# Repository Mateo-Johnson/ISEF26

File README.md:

# **EDGE-A/B Overall Design (ESP32-S3-WROOM-1-N16R8)**

**EDGE-A (Expanded Model, General):**

* Dual CPU/MCU System  
  * EDGE-A uses a single ESP32-S3 and a single RP2350 dual-core ARM Cortex-M0+, with the S3 handling high-level coordination, wireless communication (WiFi/Bluetooth), audio processing, data logging, user interface, and system management, while the RP2350 serves as the dedicated real-time processing unit for precise motor control, quadrature encoder processing, sensor fusion (gyroscope \+ TOF), PWM generation, and all timing-critical operations.  
  * The two will communicate over dedicated high speed UART  
* **ESP32-S3 based (ESP32-S3-WROOM-1)**  
  * N16R8  
  * 2.4 GHz Wifi (802.11 b/g/n)  
  * Bluetooth 5.0 (LE)  
  * USB-C (USB4085-GF-A)  
  * Interrupt-capable GPIO pins for encoders/switches  
    * Analog comparators for limit switches  
    * Hardware quadrature encoder inputs (4 channels)  
  * Low-power sleep modes  
    * Light Sleep Mode  
      * CPU is paused, RTC and ULP co-processor are running.  
      * Peripherals (like WiFi, BT) can stay connected.  
      * Wakeup sources: Timer, GPIO, ULP, etc.  
      * Lower power consumption than active mode.  
    * Deep Sleep Mode  
      * CPU, most RAM, and peripherals are powered down.  
      * Only RTC memory and ULP remain active.  
      * Very low power (tens of µA).  
      * Wakeup sources: RTC Timer, GPIO, ULP.  
* **RP2354B**  
  * External 128MB flash memory (W25Q128JVS)  
  * External Crystal (ABM8-272-T3)  
* **I/O OUT \- Check GPIO Diagram**  
  * 10 PIO pins (5 pairs) \- maximizes the RP2354B strength  
  * 2 ADC pins \- essential for motor feedback  
  * I/O can be male/female dupont  
* Distance TOF Sensor (VL53L0CXV0DH1)  
* Gyroscope (ICM-20948)  
  * Motion Interrupted Logging (MIL): only log while moving  
* USB-C/Battery Power  
  * Battery monitoring/protection circuit  
* On-board voltage regulation (3.3V, 5V, GND rails)  
* 3 PWM control channels  
  * 2 integrated DC motor drivers (DRV8833)  
* 3 Servo Connections (GND, 5V, I/O)  
* MicroSD Card Slot (TF-115)  
* 3x RGB LED (WS2812B)  
* Onboard Microphone (ICS-43434)  
* Internal USB hub IC (CH334R)  
  * Single USB-C connector routes to the hub  
  * Hub connects to both ESP32-S3 and RP2354B USB lines  
  * Each processor appears as separate COM ports on computer  
* ~~LoRa/LoRaWAN Communication (Wio-SX1262)~~  
* Battery Charger Circuit (MP2607DL-LF-Z)

**EDGE-B (Expanded Model, Machine Learning):**

* Dual CPU/MCU System  
  * EDGE-B uses a single **ESP32-S3** and a single **Kendryte K210 (Sipeed M1)**, the S3 for high-level planning, sensor fusion (gyro \+ TOF), wireless communication, audio processing, data logging, user interface, and the K210 for AI and ML applications.  
  * The two will communicate over dedicated high speed UART and distribute tasks/share larger pieces of information via shared EEPROM.  
  * Ideally, a MAIX M1 chip would be used instead of a bare K210, but if needed, a bare K210 will do.  
* **ESP32-S3 (ESP32-S3-WROOM-1)**  
  * N16R8  
  * 2.4 GHz Wifi (802.11 b/g/n)  
  * Bluetooth 5.0 (LE)  
  * USB-C (USB4085-GF-A)  
  * Interrupt-capable GPIO pins for encoders/switches  
    * Analog comparators for limit switches  
    * Hardware quadrature encoder inputs (PCNT)  
  * Low-power sleep modes  
    * Light Sleep Mode  
      * CPU is paused, RTC and ULP co-processor are running.  
      * Peripherals (like WiFi, BT) can stay connected.  
      * Wakeup sources: Timer, GPIO, ULP, etc.  
      * Lower power consumption than active mode.  
    * Deep Sleep Mode  
      * CPU, most RAM, and peripherals are powered down.  
      * Only RTC memory and ULP remain active.  
      * Very low power (tens of µA).  
      * Wakeup sources: RTC Timer, GPIO, ULP.  
* **K210 based (Sipeed MAiX module or bare chip)**  
* I/O OUT \- Check GPIO Diagram  
* Camera Input for OV2640 (FPC footprint cable)  
  * Connected to the K210  
* Gyroscope (ICM-20948)  
  * Motion Interrupted Logging (MIL): only log while moving  
* USB-C/Battery Power  
  * Battery monitoring/protection circuit  
* On-board voltage regulation (3.3V, 5V, GND rails)  
* 2 PWM control channels  
  * 2 integrated DC motor drivers (DRV8833)  
* MicroSD Card Slot (TF-115)  
* 3x RGB LED (WS2812B)  
* Onboard Microphone (ICS-43434)  
* EEPROM shared 128MB storage (CAT24M01W)  
* Ribbon Cable Input (OV2640)  
* Internal USB hub IC (CH334R)  
  * Single USB-C connector routes to the hub  
  * Hub connects to both ESP32-S3 and K210 USB lines  
  * Each processor appears as separate COM ports on computer  
* **K210** \- USB-to-UART bridge (CH340N)  
* **K210** will also need a dedicated 16MB of flash storage  
* Battery Charger Circuit (MP2607DL-LF-Z)

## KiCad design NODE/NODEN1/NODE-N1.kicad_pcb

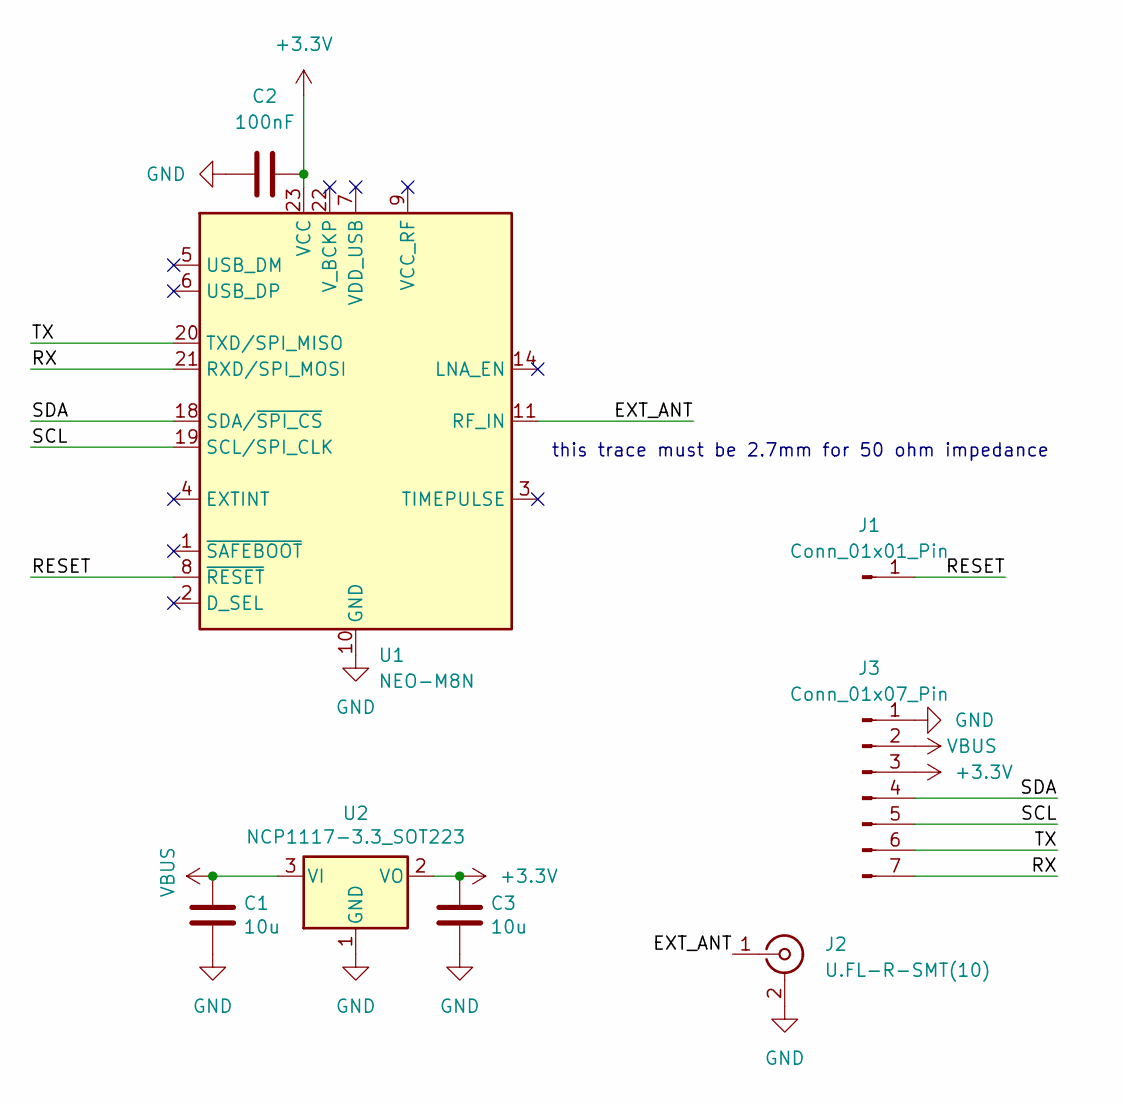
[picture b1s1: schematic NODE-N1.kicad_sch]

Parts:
C1, C3: 10u; C_0805_2012Metric
C2: 100nF; C0402
J1: Conn_01x01_Pin; TestPoint_Pad_1.5x1.5mm
J2: U.FL-R-SMT(10); U.FL_Hirose_U.FL-R-SMT-1_Vertical
J3: Conn_01x07_Pin; PinHeader_1x07_P2.54mm_Vertical
U1: NEO-M8N; ublox_NEO
U2: NCP1117-3.3_SOT223; SOT-223-3_TabPin2

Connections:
+3.3V: C2.2, C3.1, J3.3, U1.23 (VCC), U2.2 (VO)
/EXT_ANT: J2.1 (In), U1.11 (RF_IN)
/RESET: J1.1, U1.8 (~RESET)
/RX: J3.7, U1.21 (RXD/SPI_MOSI)
/SCL: J3.5, U1.19 (SCL/SPI_CLK)
/SDA: J3.4, U1.18 (SDA/~SPI_CS)
/TX: J3.6, U1.20 (TXD/SPI_MISO)
GND: C1.2, C2.1, C3.2, J2.2 (Ext), J3.1, U1.10 (GND), U1.12 (GND), U1.13 (GND), U1.24 (GND), U2.1 (GND)
VBUS: C1.1, J3.2, U2.3 (VI)

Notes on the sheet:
this trace must be 2.7mm for 50 ohm impedance

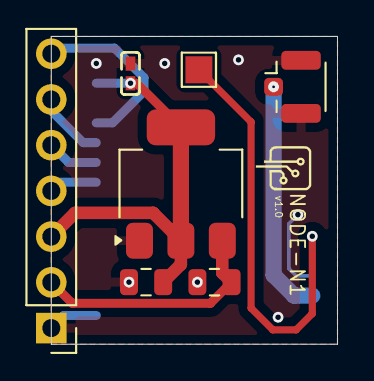
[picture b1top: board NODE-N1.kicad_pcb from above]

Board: 2 copper layers, 15.9 x 17.1 mm, 8 parts (1 on the bottom side), 9 nets.

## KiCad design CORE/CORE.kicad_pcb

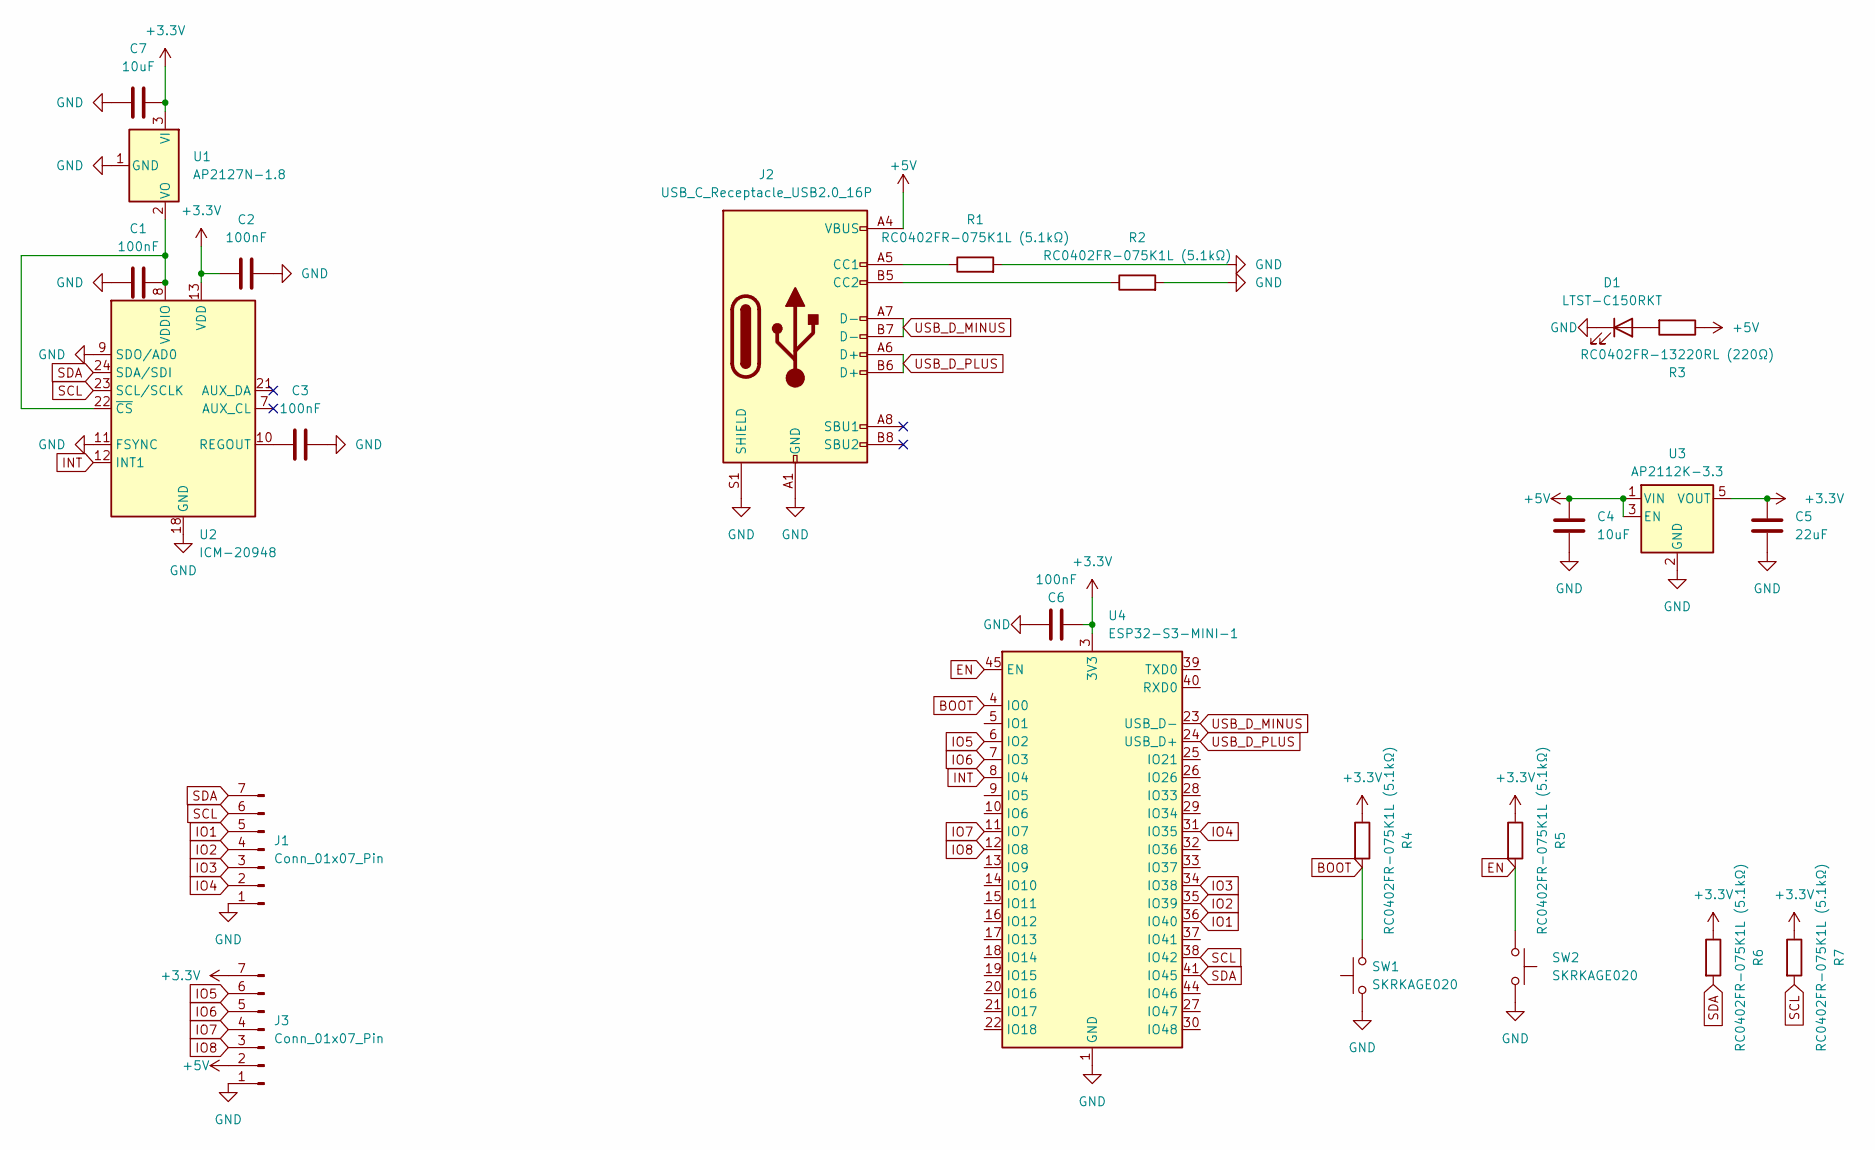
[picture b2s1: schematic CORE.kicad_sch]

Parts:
C1, C2, C3, C6: 100nF; C0402
C4, C7: 10uF; C0402
C5: 22uF; C0402
D1: LTST-C150RKT; LED_1206_3216Metric
J1, J3: Conn_01x07_Pin; PinHeader_1x07_P2.54mm_Vertical
J2: USB_C_Receptacle_USB2.0_16P; USB_C_Receptacle_HCTL_HC-TYPE-C-16P-01A
R1, R2, R4, R5, R6, R7: RC0402FR-075K1L (5.1kΩ); R0402
R3: RC0402FR-13220RL (220Ω); R0402
SW1, SW2: SKRKAGE020; SW_Push_SPST_NO_Alps_SKRK
U1: AP2127N-1.8; SOT-23
U2: ICM-20948; InvenSense_QFN-24_3x3mm_P0.4mm
U3: AP2112K-3.3; SOT-23-5
U4: ESP32-S3-MINI-1; ESP32-S2-MINI-1

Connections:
+3.3V: C2.1, C5.1, C6.2, C7.2, J3.7, R4.1, R5.1, R6.1, R7.1, U1.3 (VI), U2.13 (VDD), U3.5 (VOUT), U4.3 (3V3)
+5V: C4.1, J2.A4 (VBUS), J2.A9 (VBUS), J2.B4 (VBUS), J2.B9 (VBUS), J3.2, R3.1, U3.1 (VIN), U3.3 (EN)
BOOT: R4.2, SW1.2, U4.4 (IO0)
EN: R5.2, SW2.1, U4.45 (EN)
GND: C1.1, C2.2, C3.2, C4.2, C5.2, C6.1, C7.1, D1.1 (K), J1.1, J2.A1 (GND), J2.A12 (GND), J2.B1 (GND), J2.B12 (GND), J2.S1 (SHIELD), J3.1, R1.2, R2.2, SW1.1, SW2.2, U1.1 (GND), U2.9 (SDO/AD0), U2.11 (FSYNC), U2.18 (GND), U2.20 (GND), U3.2 (GND), U4.1 (GND), U4.2 (GND), U4.42 (GND), U4.43 (GND), U4.46 (GND), U4.47 (GND), U4.48 (GND), U4.49 (GND), U4.50 (GND), U4.51 (GND), U4.52 (GND), U4.53 (GND), U4.54 (GND), U4.55 (GND), U4.56 (GND), U4.57 (GND), U4.58 (GND), U4.59 (GND), U4.60 (GND), U4.61 (GND), U4.62 (GND), U4.63 (GND), U4.64 (GND), U4.65 (GND)
INT: U2.12 (INT1), U4.8 (IO4)
IO1: J1.5, U4.36 (IO40)
IO2: J1.4, U4.35 (IO39)
IO3: J1.3, U4.34 (IO38)
IO4: J1.2, U4.31 (IO35)
IO5: J3.6, U4.6 (IO2)
IO6: J3.5, U4.7 (IO3)
IO7: J3.4, U4.11 (IO7)
IO8: J3.3, U4.12 (IO8)
unnamed: D1.2 (A), R3.2
unnamed: J2.A5 (CC1), R1.1
unnamed: J2.B5 (CC2), R2.1
unnamed: C1.2, U1.2 (VO), U2.8 (VDDIO), U2.22 (~CS)
unnamed: C3.1, U2.10 (REGOUT)
SCL: J1.6, R7.2, U2.23 (SCL/SCLK), U4.38 (IO42)
SDA: J1.7, R6.2, U2.24 (SDA/SDI), U4.41 (IO45)
USB_D_MINUS: J2.A7 (D-), J2.B7 (D-), U4.23 (USB_D-)
USB_D_PLUS: J2.A6 (D+), J2.B6 (D+), U4.24 (USB_D+)

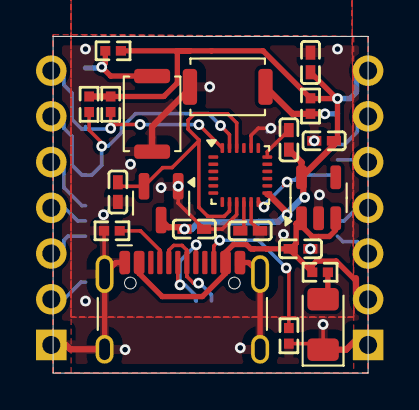
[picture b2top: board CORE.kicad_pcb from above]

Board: 2 copper layers, 17.5 x 18.7 mm, 24 parts (1 on the bottom side), 23 nets.

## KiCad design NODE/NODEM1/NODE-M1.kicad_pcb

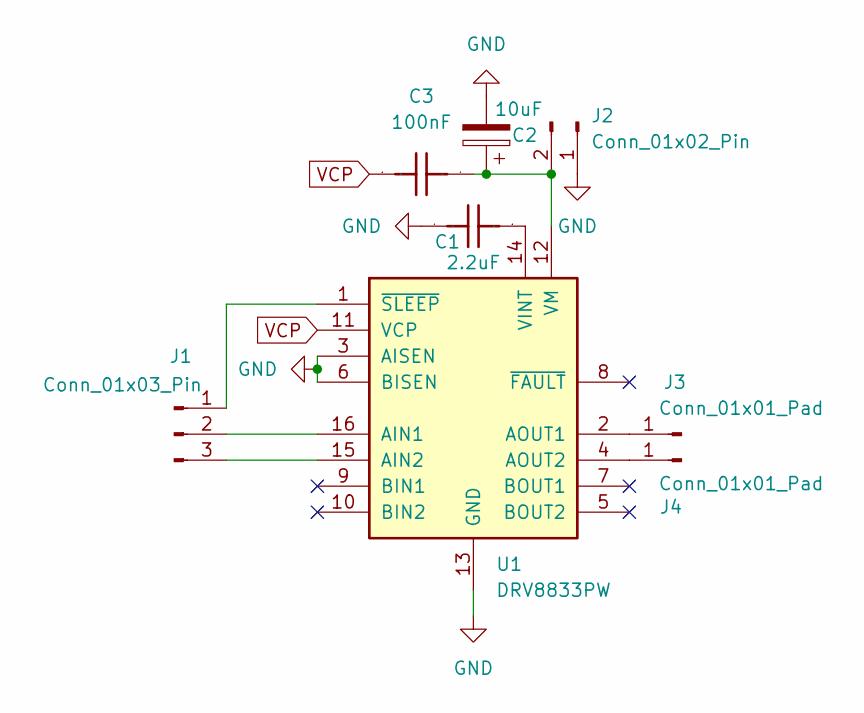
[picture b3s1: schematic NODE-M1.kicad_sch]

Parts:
C1: 2.2uF; GRM155R60J225KE01D; Manufacturer Part GRM155R60J225KE01D
C2: 10uF; TAJA106K016RNJ
C3: 100nF; CC0805KRX7R9BB104; Manufacturer Part CC0805KRX7R9BB104
J1: Conn_01x03_Pin; PinHeader_1x03_P2.54mm_Vertical
J2: Conn_01x02_Pin; PinHeader_1x02_P2.54mm_Vertical
J3, J4: Conn_01x01_Pad; TestPoint_Pad_1.5x1.5mm
U1: DRV8833PW; TSSOP-16_4.4x5mm_P0.65mm

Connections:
GND: C1.2, C2.2, J2.1, U1.3 (AISEN), U1.6 (BISEN), U1.13 (GND)
unnamed: J1.1, U1.1 (~SLEEP)
unnamed: J1.2, U1.16 (AIN1)
unnamed: J1.3, U1.15 (AIN2)
unnamed: C2.1, C3.2, J2.2, U1.12 (VM)
unnamed: J3.1, U1.2 (AOUT1)
unnamed: J4.1, U1.4 (AOUT2)
unnamed: C1.1, U1.14 (VINT)
VCP: C3.1, U1.11 (VCP)

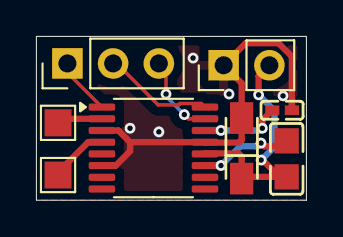
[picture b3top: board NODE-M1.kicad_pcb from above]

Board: 2 copper layers, 15.0 x 9.1 mm, 8 parts (0 on the bottom side), 9 nets.

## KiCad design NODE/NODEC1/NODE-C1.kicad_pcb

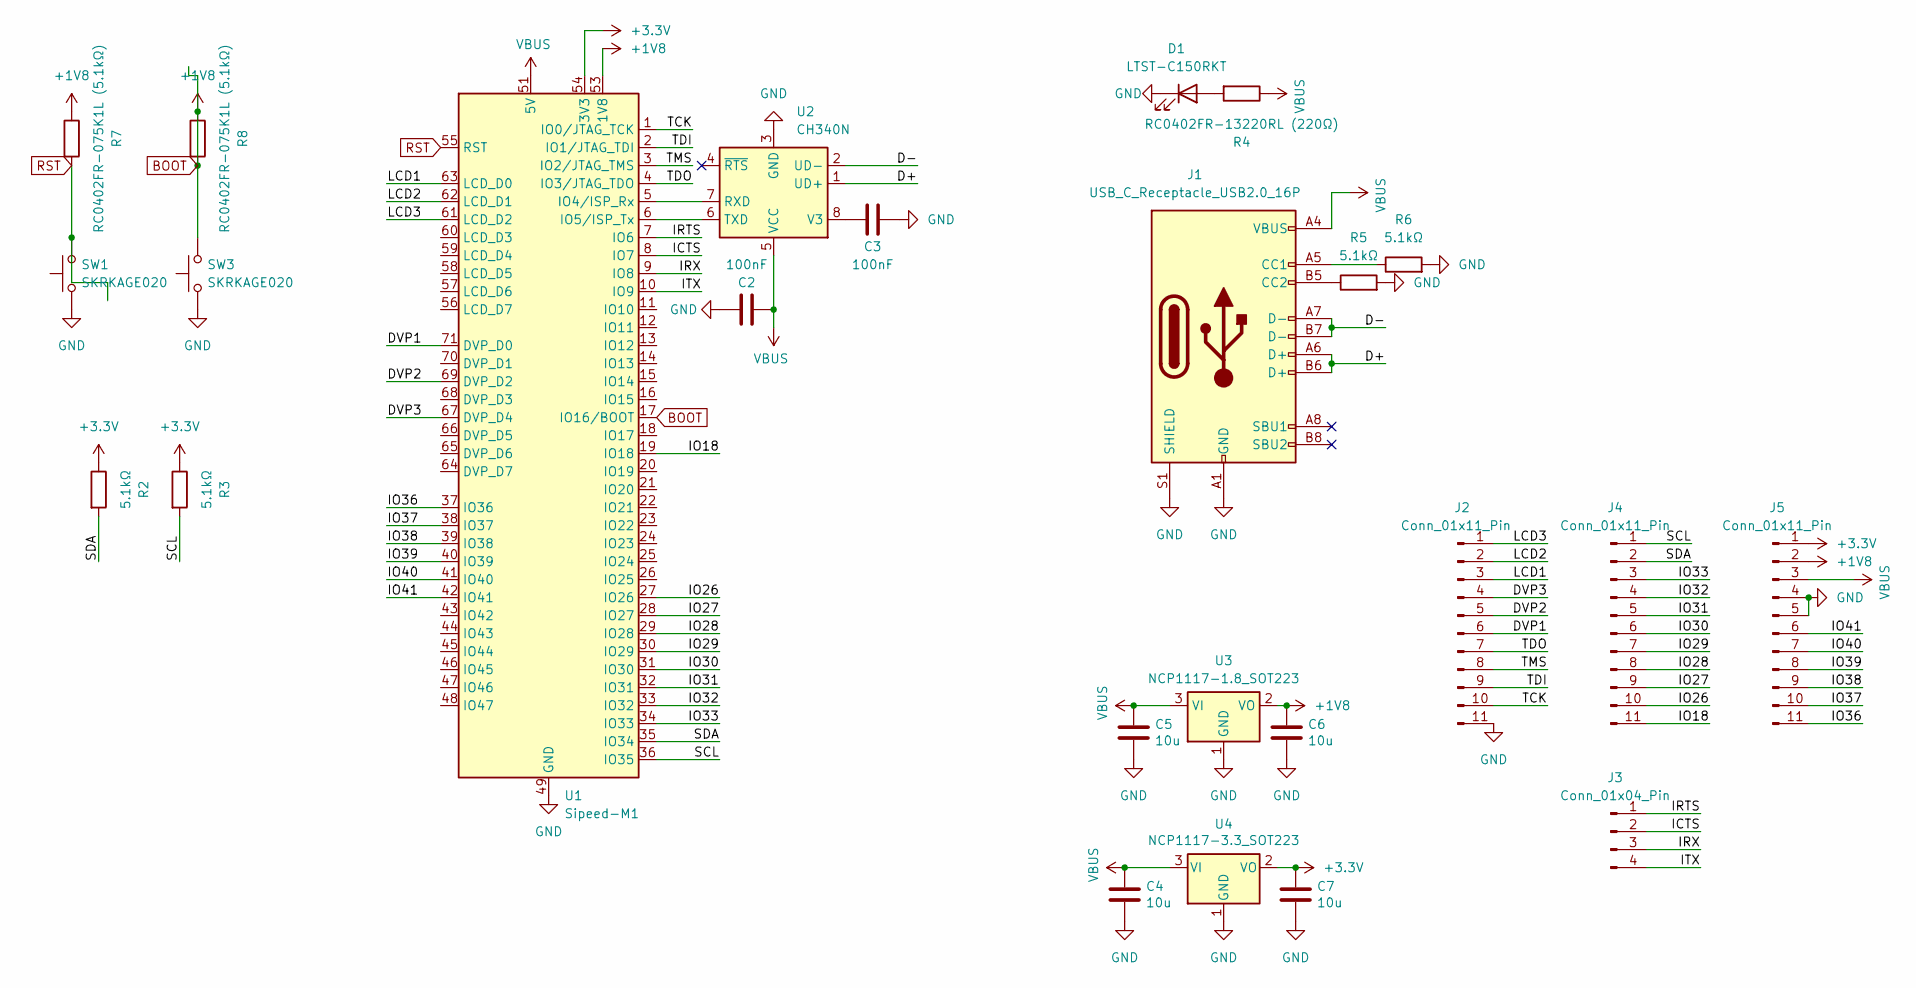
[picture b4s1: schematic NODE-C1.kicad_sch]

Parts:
C2, C3: 100nF; C0402
C4, C5, C6, C7: 10u; C_0805_2012Metric
D1: LTST-C150RKT; LED_1206_3216Metric
J1: USB_C_Receptacle_USB2.0_16P; USB_C_Receptacle_HCTL_HC-TYPE-C-16P-01A
J2, J4, J5: Conn_01x11_Pin; PinHeader_1x11_P2.54mm_Vertical
J3: Conn_01x04_Pin; PinHeader_1x04_P2.54mm_Vertical
R2, R3, R5, R6: 5.1kΩ; R0402
R4: RC0402FR-13220RL (220Ω); R0402
R7, R8: RC0402FR-075K1L (5.1kΩ); R0402
SW1, SW3: SKRKAGE020; SW_Push_SPST_NO_Alps_SKRK
U1: Sipeed-M1
U2: CH340N; SOP-8_3.9x4.9mm_P1.27mm
U3: NCP1117-1.8_SOT223; SOT-223-3_TabPin2
U4: NCP1117-3.3_SOT223; SOT-223-3_TabPin2

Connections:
+3.3V: C7.1, J5.1, R2.1, R3.1, U1.54 (3V3), U4.2 (VO)
/D+: J1.A6 (D+), J1.B6 (D+), U2.1 (UD+)
/D-: J1.A7 (D-), J1.B7 (D-), U2.2 (UD-)
/DVP1: J2.6, U1.71 (DVP_D0)
/DVP2: J2.5, U1.69 (DVP_D2)
/DVP3: J2.4, U1.67 (DVP_D4)
/ICTS: J3.2, U1.8 (IO7)
/IO18: J4.11, U1.19 (IO18)
/IO26: J4.10, U1.27 (IO26)
/IO27: J4.9, U1.28 (IO27)
/IO28: J4.8, U1.29 (IO28)
/IO29: J4.7, U1.30 (IO29)
/IO30: J4.6, U1.31 (IO30)
/IO31: J4.5, U1.32 (IO31)
/IO32: J4.4, U1.33 (IO32)
/IO33: J4.3, U1.34 (IO33)
/IO36: J5.11, U1.37 (IO36)
/IO37: J5.10, U1.38 (IO37)
/IO38: J5.9, U1.39 (IO38)
/IO39: J5.8, U1.40 (IO39)
/IO40: J5.7, U1.41 (IO40)
/IO41: J5.6, U1.42 (IO41)
/IRTS: J3.1, U1.7 (IO6)
/IRX: J3.3, U1.9 (IO8)
/ITX: J3.4, U1.10 (IO9)
/LCD1: J2.3, U1.63 (LCD_D0)
/LCD2: J2.2, U1.62 (LCD_D1)
/LCD3: J2.1, U1.61 (LCD_D2)
/SCL: J4.1, R3.2, U1.36 (IO35)
/SDA: J4.2, R2.2, U1.35 (IO34)
/TCK: J2.10, U1.1 (IO0/JTAG_TCK)
/TDI: J2.9, U1.2 (IO1/JTAG_TDI)
/TDO: J2.7, U1.4 (IO3/JTAG_TDO)
/TMS: J2.8, U1.3 (IO2/JTAG_TMS)
GND: C2.1, C3.1, C4.2, C5.2, C6.2, C7.2, D1.1 (K), J1.A1 (GND), J1.A12 (GND), J1.B1 (GND), J1.B12 (GND), J1.S1 (SHIELD), J2.11, J5.4, J5.5, R5.2, R6.2, SW1.1, SW3.1, U1.49 (GND), U1.50 (GND), U1.72 (GND), U2.3 (GND), U3.1 (GND), U4.1 (GND); also elsewhere on the board
unnamed: D1.2 (A), R4.2
unnamed: J1.A5 (CC1), R6.1
unnamed: J1.B5 (CC2), R5.1
unnamed: U1.5 (IO4/ISP_Rx), U2.7 (RXD)
unnamed: U1.6 (IO5/ISP_Tx), U2.6 (TXD)
unnamed: C3.2, U2.8 (V3)
RST: R7.2, SW1.2, U1.55 (RST); also elsewhere on the board
VBUS: C2.2, C4.1, C5.1, J1.A4 (VBUS), J1.A9 (VBUS), J1.B4 (VBUS), J1.B9 (VBUS), J5.3, R4.1, U1.51 (5V), U1.52 (5V), U2.5 (VCC), U3.3 (VI), U4.3 (VI)

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
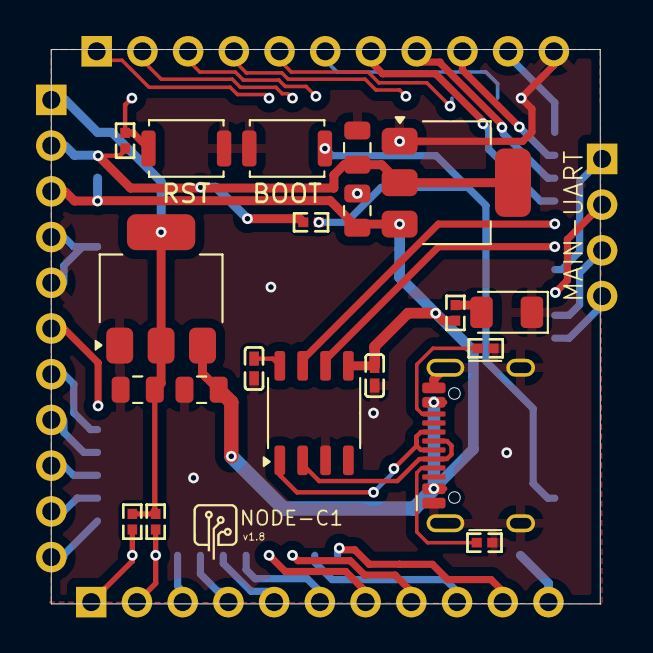
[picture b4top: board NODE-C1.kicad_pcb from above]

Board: 2 copper layers, 30.5 x 30.8 mm, 25 parts (1 on the bottom side), 45 nets.

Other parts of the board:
BOOT: SKRKAGE020; SW_Push_SPST_NO_Alps_SKRK
RST: SKRKAGE020; SW_Push_SPST_NO_Alps_SKRK

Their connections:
GND: BOOT.1, RST.1; also elsewhere on the board
RST: RST.2; also elsewhere on the board

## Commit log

2025-11-03 add node C1 files
2025-11-03 Add files via upload
    add node m1 files
2025-11-03 Document EDGE-A/B overall design specifications
    Added detailed design specifications for EDGE-A and EDGE-B models, including hardware components and functionalities.
2025-11-18 Add SVG image to README
2025-11-18 Include image tag for quad chart
    Add image tag for quad chart in README
2025-11-18 Replace Quad Chart image with new version
    Updated the image for the Quad Chart in README.
